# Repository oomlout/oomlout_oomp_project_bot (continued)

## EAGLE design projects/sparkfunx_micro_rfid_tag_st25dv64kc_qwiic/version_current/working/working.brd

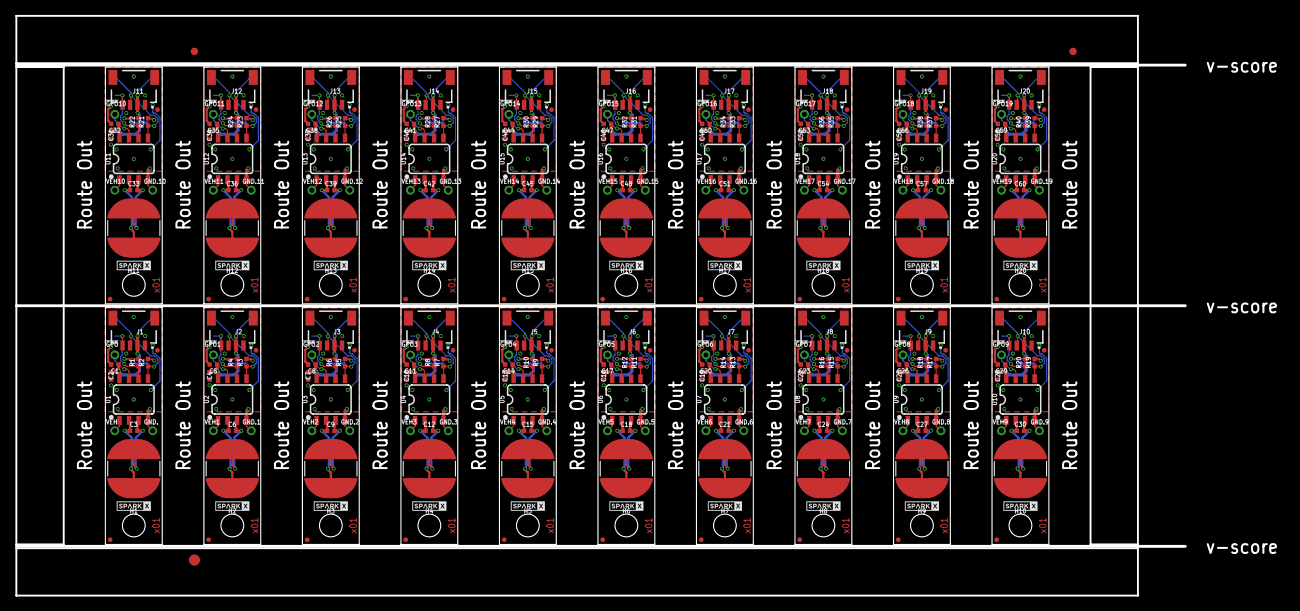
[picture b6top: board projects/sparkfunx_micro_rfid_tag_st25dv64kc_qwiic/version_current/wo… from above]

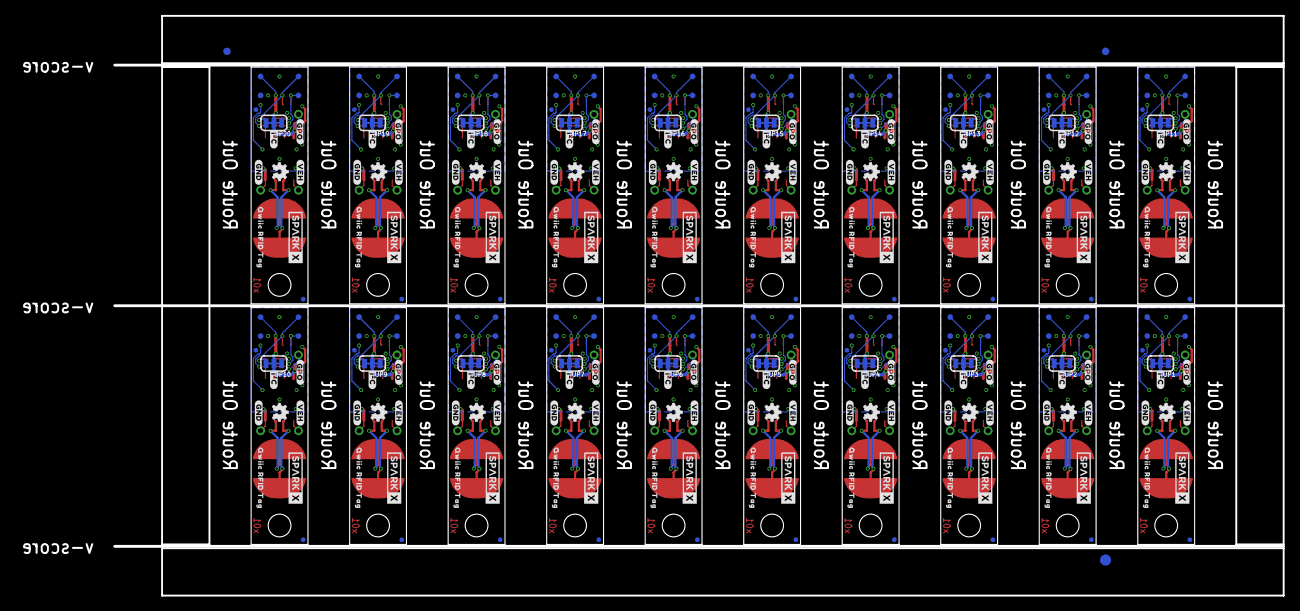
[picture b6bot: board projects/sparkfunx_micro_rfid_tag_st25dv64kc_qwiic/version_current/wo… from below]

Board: 2 copper layers, 156.7 x 77.7 mm, 586 parts (283 on the bottom side), 200 nets.

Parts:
3V1, 3V2, 3V3, 3V4, 3V5, 3V6, 3V7, 3V8, 3V9, 3V10, 3V11, 3V12, 3V13, 3V14, 3V15, 3V16, 3V17, 3V18, 3V19, 3V20: TEST-POINT3; PAD.03X.03
!GPO!, !GPO!1, !GPO!2, !GPO!3, !GPO!4, !GPO!5, !GPO!6, !GPO!7, !GPO!8, !GPO!9, !GPO!10, !GPO!11, !GPO!12, !GPO!13, !GPO!14, !GPO!15, !GPO!16, !GPO!17, !GPO!18, !GPO!19: 1X01_1MM_NO_SILK
ANT, ANT1, ANT2, ANT3, ANT4, ANT5, ANT6, ANT7, ANT8, ANT9, ANT10, ANT11, ANT12, ANT13, ANT14, ANT15, ANT16, ANT17, ANT18, ANT19: 4.7μH; W3102
C1, C5, C8, C11, C14, C17, C20, C23, C26, C29, C32, C35, C38, C41, C44, C47, C50, C53, C56, C59: 0.1uF; 0402-TIGHT
C2, C4, C7, C10, C13, C16, C19, C22, C25, C28, C31, C34, C37, C40, C43, C46, C49, C52, C55, C58: 2.2uF; 0402-TIGHT
C3, C6, C9, C12, C15, C18, C21, C24, C27, C30, C33, C36, C39, C42, C45, C48, C51, C54, C57, C60: 0.5pF; 0402-TIGHT
E$1, E$2, E$3, E$4: FIDUCIAL-1X2
E$5, E$6: FIDUCIAL-1.5X3
FD1, FD2, FD3, FD4, FD5, FD6, FD7, FD8, FD9, FD10, FD11, FD12, FD13, FD14, FD15, FD16, FD17, FD18, FD19, FD20, FD21, FD22, FD23, FD24, FD25, FD26, FD27, FD28, FD29, FD30, FD31, FD32, FD33, FD34, FD35, FD36, FD37, FD38, FD39, FD40, FD41, FD42, FD43, FD44, FD45, FD46, FD47, FD48, FD49, FD50, FD51, FD52, FD53, FD54, FD55, FD56, FD57, FD58, FD59, FD60, FD61, FD62, FD63, FD64, FD65, FD66, FD67, FD68, FD69, FD70, FD71, FD72, FD73, FD74, FD75, FD76, FD77, FD78, FD79, FD80: FIDUCIALUFIDUCIAL; FIDUCIAL-MICRO
GND, GND1, GND2, GND3, GND4, GND5, GND6, GND7, GND8, GND9, GND10, GND11, GND12, GND13, GND14, GND15, GND16, GND17, GND18, GND19: TEST-POINT3; PAD.03X.03
GND., GND.1, GND.2, GND.3, GND.4, GND.5, GND.6, GND.7, GND.8, GND.9, GND.10, GND.11, GND.12, GND.13, GND.14, GND.15, GND.16, GND.17, GND.18, GND.19: 1X01_1MM_NO_SILK
H1, H2, H3, H4, H5, H6, H7, H8, H9, H10, H11, H12, H13, H14, H15, H16, H17, H18, H19, H20: STAND-OFFTIGHT; STAND-OFF-TIGHT
J1, J2, J3, J4, J5, J6, J7, J8, J9, J10, J11, J12, J13, J14, J15, J16, J17, J18, J19, J20: QWIIC_RIGHT_ANGLE; JST04_1MM_RA
JP1, JP2, JP3, JP4, JP5, JP6, JP7, JP8, JP9, JP10, JP11, JP12, JP13, JP14, JP15, JP16, JP17, JP18, JP19, JP20: JUMPER-SMT_3_2-NC_TRACE_SILK; SMT-JUMPER_3_2-NC_TRACE_SILK
LOGO1, LOGO2, LOGO3, LOGO4, LOGO5, LOGO6, LOGO7, LOGO8, LOGO9, LOGO10, LOGO11, LOGO12, LOGO13, LOGO14, LOGO15, LOGO16, LOGO17, LOGO18, LOGO19, LOGO20: OSHW-LOGOMINI; OSHW-LOGO-MINI
R1, R2, R3, R4, R5, R6, R7, R8, R9, R10, R11, R12, R13, R14, R15, R16, R17, R18, R19, R20, R21, R22, R23, R24, R25, R26, R27, R28, R29, R30, R31, R32, R33, R34, R35, R36, R37, R38, R39, R40: 2.2k; 0402-TIGHT
SCL, SCL1, SCL2, SCL3, SCL4, SCL5, SCL6, SCL7, SCL8, SCL9, SCL10, SCL11, SCL12, SCL13, SCL14, SCL15, SCL16, SCL17, SCL18, SCL19: TEST-POINT3; PAD.03X.03
SDA, SDA1, SDA2, SDA3, SDA4, SDA5, SDA6, SDA7, SDA8, SDA9, SDA10, SDA11, SDA12, SDA13, SDA14, SDA15, SDA16, SDA17, SDA18, SDA19: TEST-POINT3; PAD.03X.03
U1, U2, U3, U4, U5, U6, U7, U8, U9, U10, U11, U12, U13, U14, U15, U16, U17, U18, U19, U20: ST25DV64KC; SO08
U$1, U$7, U$14, U$22, U$29, U$36, U$43, U$50, U$57, U$64, U$71, U$78, U$85, U$92, U$99, U$106, U$113, U$120, U$127, U$134: SPARKX-LOGO2; SPARKX-TINY
U$2, U$10, U$17, U$25, U$32, U$39, U$46, U$53, U$60, U$67, U$74, U$81, U$88, U$95, U$102, U$109, U$116, U$123, U$130, U$137: ##GPO##0
U$3, U$13, U$21, U$28, U$35, U$42, U$49, U$56, U$63, U$70, U$77, U$84, U$91, U$98, U$105, U$112, U$119, U$126, U$133, U$140: QWIIC_RFID_TAG0
U$4, U$11, U$18, U$26, U$33, U$40, U$47, U$54, U$61, U$68, U$75, U$82, U$89, U$96, U$103, U$110, U$117, U$124, U$131, U$138: #VEH#0
U$5, U$9, U$16, U$24, U$31, U$38, U$45, U$52, U$59, U$66, U$73, U$80, U$87, U$94, U$101, U$108, U$115, U$122, U$129, U$136: #I�C#0
U$6, U$12, U$19, U$27, U$34, U$41, U$48, U$55, U$62, U$69, U$76, U$83, U$90, U$97, U$104, U$111, U$118, U$125, U$132, U$139: #GND#0
U$8, U$15, U$20, U$23, U$30, U$37, U$44, U$51, U$58, U$65, U$72, U$79, U$86, U$93, U$100, U$107, U$114, U$121, U$128, U$135: SPARKX-LOGO3; SPARKX-SMALL
VEH, VEH1, VEH2, VEH3, VEH4, VEH5, VEH6, VEH7, VEH8, VEH9, VEH10, VEH11, VEH12, VEH13, VEH14, VEH15, VEH16, VEH17, VEH18, VEH19: 1X01_1MM_NO_SILK

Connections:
3.3V: 3V3.1, C1.1, C2.1, J1.2, JP1.2, U1.8
3.3V1: 3V1.1, C4.1, C5.1, J2.2, JP2.2, U2.8
3.3V2: 3V2.1, C7.1, C8.1, J3.2, JP3.2, U3.8
3.3V3: 3V4.1, C10.1, C11.1, J4.2, JP4.2, U4.8
3.3V4: 3V5.1, C13.1, C14.1, J5.2, JP5.2, U5.8
3.3V5: 3V6.1, C16.1, C17.1, J6.2, JP6.2, U6.8
3.3V6: 3V7.1, C19.1, C20.1, J7.2, JP7.2, U7.8
3.3V7: 3V8.1, C22.1, C23.1, J8.2, JP8.2, U8.8
3.3V8: 3V9.1, C25.1, C26.1, J9.2, JP9.2, U9.8
3.3V9: 3V10.1, C28.1, C29.1, J10.2, JP10.2, U10.8
3.3V10: 3V11.1, C31.1, C32.1, J11.2, JP11.2, U11.8
3.3V11: 3V12.1, C34.1, C35.1, J12.2, JP12.2, U12.8
3.3V12: 3V13.1, C37.1, C38.1, J13.2, JP13.2, U13.8
3.3V13: 3V14.1, C40.1, C41.1, J14.2, JP14.2, U14.8
3.3V14: 3V15.1, C43.1, C44.1, J15.2, JP15.2, U15.8
3.3V15: 3V16.1, C46.1, C47.1, J16.2, JP16.2, U16.8
3.3V16: 3V17.1, C49.1, C50.1, J17.2, JP17.2, U17.8
3.3V17: 3V18.1, C52.1, C53.1, J18.2, JP18.2, U18.8
3.3V18: 3V19.1, C55.1, C56.1, J19.2, JP19.2, U19.8
3.3V19: 3V20.1, C58.1, C59.1, J20.2, JP20.2, U20.8
!GPO!: !GPO!.1, U1.7
!GPO!1: !GPO!1.1, U2.7
!GPO!2: !GPO!2.1, U3.7
!GPO!3: !GPO!3.1, U4.7
!GPO!4: !GPO!4.1, U5.7
!GPO!5: !GPO!5.1, U6.7
!GPO!6: !GPO!6.1, U7.7
!GPO!7: !GPO!7.1, U8.7
!GPO!8: !GPO!8.1, U9.7
!GPO!9: !GPO!9.1, U10.7
!GPO!10: !GPO!10.1, U11.7
!GPO!11: !GPO!11.1, U12.7
!GPO!12: !GPO!12.1, U13.7
!GPO!13: !GPO!13.1, U14.7
!GPO!14: !GPO!14.1, U15.7
!GPO!15: !GPO!15.1, U16.7
!GPO!16: !GPO!16.1, U17.7
!GPO!17: !GPO!17.1, U18.7
!GPO!18: !GPO!18.1, U19.7
!GPO!19: !GPO!19.1, U20.7
GND: C1.2, C2.2, GND.1, GND..1, J1.1, U1.4
GND1: C4.2, C5.2, GND1.1, GND.1.1, J2.1, U2.4
GND2: C7.2, C8.2, GND2.1, GND.2.1, J3.1, U3.4
GND3: C10.2, C11.2, GND3.1, GND.3.1, J4.1, U4.4
GND4: C13.2, C14.2, GND4.1, GND.4.1, J5.1, U5.4
GND5: C16.2, C17.2, GND5.1, GND.5.1, J6.1, U6.4
GND6: C19.2, C20.2, GND6.1, GND.6.1, J7.1, U7.4
GND7: C22.2, C23.2, GND7.1, GND.7.1, J8.1, U8.4
GND8: C25.2, C26.2, GND8.1, GND.8.1, J9.1, U9.4
GND9: C28.2, C29.2, GND9.1, GND.9.1, J10.1, U10.4
GND10: C31.2, C32.2, GND10.1, GND.10.1, J11.1, U11.4
GND11: C34.2, C35.2, GND11.1, GND.11.1, J12.1, U12.4
GND12: C37.2, C38.2, GND12.1, GND.12.1, J13.1, U13.4
GND13: C40.2, C41.2, GND13.1, GND.13.1, J14.1, U14.4
GND14: C43.2, C44.2, GND14.1, GND.14.1, J15.1, U15.4
GND15: C46.2, C47.2, GND15.1, GND.15.1, J16.1, U16.4
GND16: C49.2, C50.2, GND16.1, GND.16.1, J17.1, U17.4
GND17: C52.2, C53.2, GND17.1, GND.17.1, J18.1, U18.4
GND18: C55.2, C56.2, GND18.1, GND.18.1, J19.1, U19.4
GND19: C58.2, C59.2, GND19.1, GND.19.1, J20.1, U20.4
unnamed: ANT.2, C3.2, U1.3
unnamed: ANT.1, C3.1, U1.2
unnamed: JP1.3, R2.2
unnamed: JP1.1, R1.2
unnamed: ANT1.2, C6.2, U2.3
unnamed: ANT1.1, C6.1, U2.2
unnamed: JP2.3, R3.2
unnamed: JP2.1, R4.2
unnamed: ANT2.2, C9.2, U3.3
unnamed: ANT2.1, C9.1, U3.2
unnamed: JP3.3, R5.2
unnamed: JP3.1, R6.2
unnamed: ANT3.2, C12.2, U4.3
unnamed: ANT3.1, C12.1, U4.2
unnamed: JP4.3, R7.2
unnamed: JP4.1, R8.2
unnamed: ANT4.2, C15.2, U5.3
unnamed: ANT4.1, C15.1, U5.2
unnamed: JP5.3, R9.2
unnamed: JP5.1, R10.2
unnamed: ANT5.2, C18.2, U6.3
unnamed: ANT5.1, C18.1, U6.2
unnamed: JP6.3, R11.2
unnamed: JP6.1, R12.2
unnamed: ANT6.2, C21.2, U7.3
unnamed: ANT6.1, C21.1, U7.2
unnamed: JP7.3, R13.2
unnamed: JP7.1, R14.2
unnamed: ANT7.2, C24.2, U8.3
unnamed: ANT7.1, C24.1, U8.2
unnamed: JP8.3, R15.2
unnamed: JP8.1, R16.2
unnamed: ANT8.2, C27.2, U9.3
unnamed: ANT8.1, C27.1, U9.2
unnamed: JP9.3, R17.2
unnamed: JP9.1, R18.2
unnamed: ANT9.2, C30.2, U10.3
unnamed: ANT9.1, C30.1, U10.2
unnamed: JP10.3, R19.2
unnamed: JP10.1, R20.2
unnamed: ANT10.2, C33.2, U11.3
unnamed: ANT10.1, C33.1, U11.2
unnamed: JP11.3, R21.2
unnamed: JP11.1, R22.2
unnamed: ANT11.2, C36.2, U12.3
unnamed: ANT11.1, C36.1, U12.2
unnamed: JP12.3, R23.2
unnamed: JP12.1, R24.2
unnamed: ANT12.2, C39.2, U13.3
unnamed: ANT12.1, C39.1, U13.2
unnamed: JP13.3, R25.2
unnamed: JP13.1, R26.2
unnamed: ANT13.2, C42.2, U14.3
unnamed: ANT13.1, C42.1, U14.2
unnamed: JP14.3, R27.2
unnamed: JP14.1, R28.2
unnamed: ANT14.2, C45.2, U15.3
unnamed: ANT14.1, C45.1, U15.2
unnamed: JP15.3, R29.2
unnamed: JP15.1, R30.2
unnamed: ANT15.2, C48.2, U16.3
unnamed: ANT15.1, C48.1, U16.2
unnamed: JP16.3, R31.2
unnamed: JP16.1, R32.2
unnamed: ANT16.2, C51.2, U17.3
unnamed: ANT16.1, C51.1, U17.2
unnamed: JP17.3, R33.2
unnamed: JP17.1, R34.2
unnamed: ANT17.2, C54.2, U18.3
unnamed: ANT17.1, C54.1, U18.2
unnamed: JP18.3, R35.2
unnamed: JP18.1, R36.2
unnamed: ANT18.2, C57.2, U19.3
unnamed: ANT18.1, C57.1, U19.2
unnamed: JP19.3, R37.2
unnamed: JP19.1, R38.2
unnamed: ANT19.2, C60.2, U20.3
unnamed: ANT19.1, C60.1, U20.2
unnamed: JP20.3, R39.2
unnamed: JP20.1, R40.2
SCL: J1.4, R1.1, SCL.1, U1.6
SCL1: J2.4, R4.1, SCL1.1, U2.6
SCL2: J3.4, R6.1, SCL2.1, U3.6
SCL3: J4.4, R8.1, SCL3.1, U4.6
SCL4: J5.4, R10.1, SCL4.1, U5.6
SCL5: J6.4, R12.1, SCL5.1, U6.6
SCL6: J7.4, R14.1, SCL6.1, U7.6
SCL7: J8.4, R16.1, SCL7.1, U8.6
SCL8: J9.4, R18.1, SCL8.1, U9.6
SCL9: J10.4, R20.1, SCL9.1, U10.6
SCL10: J11.4, R22.1, SCL10.1, U11.6
SCL11: J12.4, R24.1, SCL11.1, U12.6
SCL12: J13.4, R26.1, SCL12.1, U13.6
SCL13: J14.4, R28.1, SCL13.1, U14.6
SCL14: J15.4, R30.1, SCL14.1, U15.6
SCL15: J16.4, R32.1, SCL15.1, U16.6
SCL16: J17.4, R34.1, SCL16.1, U17.6
SCL17: J18.4, R36.1, SCL17.1, U18.6
SCL18: J19.4, R38.1, SCL18.1, U19.6
SCL19: J20.4, R40.1, SCL19.1, U20.6
SDA: J1.3, R2.1, SDA.1, U1.5
SDA1: J2.3, R3.1, SDA1.1, U2.5
SDA2: J3.3, R5.1, SDA2.1, U3.5
SDA3: J4.3, R7.1, SDA3.1, U4.5
SDA4: J5.3, R9.1, SDA4.1, U5.5
SDA5: J6.3, R11.1, SDA5.1, U6.5
SDA6: J7.3, R13.1, SDA6.1, U7.5
SDA7: J8.3, R15.1, SDA7.1, U8.5
SDA8: J9.3, R17.1, SDA8.1, U9.5
SDA9: J10.3, R19.1, SDA9.1, U10.5
SDA10: J11.3, R21.1, SDA10.1, U11.5
SDA11: J12.3, R23.1, SDA11.1, U12.5
SDA12: J13.3, R25.1, SDA12.1, U13.5
SDA13: J14.3, R27.1, SDA13.1, U14.5
SDA14: J15.3, R29.1, SDA14.1, U15.5
SDA15: J16.3, R31.1, SDA15.1, U16.5
SDA16: J17.3, R33.1, SDA16.1, U17.5
SDA17: J18.3, R35.1, SDA17.1, U18.5
SDA18: J19.3, R37.1, SDA18.1, U19.5
SDA19: J20.3, R39.1, SDA19.1, U20.5
VEH: U1.1, VEH.1
VEH1: U2.1, VEH1.1
VEH2: U3.1, VEH2.1
VEH3: U4.1, VEH3.1
VEH4: U5.1, VEH4.1
VEH5: U6.1, VEH5.1
VEH6: U7.1, VEH6.1
VEH7: U8.1, VEH7.1
VEH8: U9.1, VEH8.1
VEH9: U10.1, VEH9.1
VEH10: U11.1, VEH10.1
VEH11: U12.1, VEH11.1
VEH12: U13.1, VEH12.1
VEH13: U14.1, VEH13.1
VEH14: U15.1, VEH14.1
VEH15: U16.1, VEH15.1
VEH16: U17.1, VEH16.1
VEH17: U18.1, VEH17.1
VEH18: U19.1, VEH18.1
VEH19: U20.1, VEH19.1

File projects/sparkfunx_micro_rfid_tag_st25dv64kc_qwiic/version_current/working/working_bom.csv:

"Id";"Designator";"Footprint";"Quantity";"Designation";"Supplier and ref";
1;"R16,R22,R8,R3,R33,R5,R14,R18,R4,R21,R23,R31,R40,R37,R7,R38,R2,R13,R17,R9,R32,R6,R15,R11,R28,R19,R36,R29,R12,R20,R1,R30,R25,R26,R39,R10,R24,R27,R34,R35";"0402-TIGHT";40;"2.2k";;;
2;"FD53,FD51,FD25,FD13,FD9,FD47,FD31,FD37,FD15,FD3,FD67,FD55,FD71,FD29,FD75,FD19,FD33,FD41,FD11,FD7,FD59,FD5,FD69,FD63,FD17,FD43,FD49,FD57,FD27,FD45,FD65,FD23,FD61,FD39,FD73,FD1,FD77,FD21,FD79,FD35,FD20,FD58,FD26,FD18,FD66,FD52,FD40,FD38,FD12,FD72,FD36,FD16,FD28,FD10,FD32,FD48,FD42,FD30,FD68,FD64,FD76,FD80,FD74,FD56,FD24,FD46,FD34,FD8,FD22,FD54,FD70,FD60,FD14,FD6,FD2,FD78,FD44,FD62,FD4,FD50";"FIDUCIAL-MICRO";80;"FIDUCIALUFIDUCIAL";;;
3;"H1,H14,H20,H8,H3,H9,H18,H17,H4,H12,H13,H11,H2,H19,H15,H6,H10,H7,H5,H16";"STAND-OFF-TIGHT";20;"STAND-OFFTIGHT";;;
4;"GND.18,VEH10,GND.13,VEH12,GND.4,GND.7,GND.10,!GPO!3,!GPO!18,!GPO!7,VEH16,VEH4,GND.12,GND.14,VEH3,VEH6,!GPO!13,!GPO!2,!GPO!0,VEH8,!GPO!15,GND.0,!GPO!19,VEH13,GND.1,VEH1,VEH7,!GPO!8,VEH2,GND.11,!GPO!5,GND.16,GND.8,VEH11,!GPO!12,VEH9,VEH17,!GPO!6,!GPO!11,VEH14,!GPO!1,VEH18,GND.6,GND.5,!GPO!9,GND.15,VEH15,GND.17,!GPO!16,VEH0,!GPO!14,!GPO!17,GND.2,GND.9,!GPO!4,GND.19,GND.3,!GPO!10,VEH19,VEH5";"1X01_1MM_NO_SILK";60;"";;;
5;"U$120,U$99,U$43,U$113,U$127,U$14,U$71,U$7,U$57,U$50,U$22,U$78,U$92,U$64,U$85,U$29,U$106,U$134,U$36,U$1";"SPARKX-TINY";20;"SPARKX-LOGO2";;;
6;"C39,C60,C42,C30,C45,C51,C3,C21,C12,C48,C9,C33,C57,C18,C36,C27,C24,C54,C15,C6";"0402-TIGHT";20;"0.5pF";;;
7;"U1,U20,U2,U12,U8,U6,U10,U17,U4,U11,U13,U16,U18,U9,U15,U3,U14,U19,U7,U5";"SO08";20;"ST25DV64KC";;;
8;"C11,C41,C29,C8,C17,C44,C53,C50,C59,C20,C38,C26,C47,C5,C32,C56,C23,C14,C35,C1";"0402-TIGHT";20;"0.1uF";;;
9;"J9,J2,J17,J6,J10,J20,J13,J8,J15,J14,J11,J18,J3,J4,J19,J1,J16,J5,J12,J7";"JST04_1MM_RA";20;"QWIIC_RIGHT_ANGLE";;;
10;"ANT19,ANT18,ANT16,ANT12,ANT9,ANT0,ANT3,ANT17,ANT11,ANT15,ANT8,ANT5,ANT10,ANT14,ANT7,ANT13,ANT6,ANT4,ANT1,ANT2";"W3102";20;"4.7μH";;;
11;"C58,C7,C2,C37,C19,C46,C25,C22,C4,C31,C28,C52,C40,C49,C43,C13,C34,C16,C10,C55";"0402-TIGHT";20;"2.2uF";;;
12;"E$3,E$1,E$4,E$2";"FIDUCIAL-1X2";4;"";;;
13;"E$5,E$6";"FIDUCIAL-1.5X3";2;"";;;
14;"SDA19,UNK3V14,UNK3V12,UNK3V20,UNK3V5,UNK3V3,SDA6,UNK3V13,GND15,SCL2,SCL15,UNK3V18,GND3,GND0,GND2,SCL12,GND14,SDA12,SDA1,GND10,SCL7,GND5,GND6,SDA2,SCL0,SCL5,SCL11,SDA18,UNK3V11,SCL4,SDA14,GND4,GND17,GND19,SCL13,UNK3V10,GND16,SDA3,SCL6,SCL10,UNK3V8,UNK3V17,SDA8,SDA13,SCL8,SDA11,SCL1,SCL9,GND7,SCL19,SDA9,SDA5,SDA15,SDA4,UNK3V4,GND9,SDA17,UNK3V7,SCL16,UNK3V9,UNK3V16,SDA7,SDA16,UNK3V2,SCL3,GND13,SCL14,GND11,SDA10,SDA0,GND1,UNK3V19,SCL17,GND18,UNK3V6,UNK3V1,SCL18,GND12,GND8,UNK3V15";"PAD.03X.03";80;"TEST-POINT3";;;
15;"U$105,U$3,U$13,U$21,U$126,U$70,U$28,U$98,U$77,U$63,U$91,U$112,U$119,U$133,U$35,U$84,U$42,U$140,U$49,U$56";"QWIIC_RFID_TAG0";20;"";;;
16;"U$41,U$69,U$139,U$90,U$76,U$34,U$125,U$104,U$132,U$12,U$55,U$62,U$83,U$118,U$19,U$97,U$48,U$111,U$27,U$6";"#GND#0";20;"";;;
17;"LOGO12,LOGO16,LOGO1,LOGO17,LOGO11,LOGO9,LOGO14,LOGO7,LOGO2,LOGO19,LOGO3,LOGO18,LOGO6,LOGO13,LOGO4,LOGO15,LOGO10,LOGO20,LOGO5,LOGO8";"OSHW-LOGO-MINI";20;"OSHW-LOGOMINI";;;
18;"U$38,U$5,U$66,U$101,U$59,U$94,U$122,U$108,U$136,U$115,U$129,U$16,U$52,U$31,U$80,U$87,U$73,U$24,U$9,U$45";"#I�C#0";20;"";;;
19;"U$30,U$20,U$121,U$65,U$114,U$23,U$51,U$128,U$86,U$93,U$107,U$8,U$100,U$15,U$58,U$135,U$72,U$44,U$79,U$37";"SPARKX-SMALL";20;"SPARKX-LOGO3";;;
20;"U$53,U$137,U$17,U$32,U$39,U$67,U$60,U$81,U$109,U$95,U$25,U$74,U$130,U$10,U$123,U$102,U$116,U$2,U$88,U$46";"##GPO##0";20;"";;;
21;"JP6,JP9,JP7,JP14,JP8,JP3,JP1,JP11,JP20,JP2,JP4,JP13,JP17,JP16,JP19,JP5,JP12,JP15,JP18,JP10";"SMT-JUMPER_3_2-NC_TRACE_SILK";20;"JUMPER-SMT_3_2-NC_TRACE_SILK";;;
22;"U$18,U$11,U$4,U$89,U$61,U$124,U$110,U$33,U$26,U$138,U$75,U$68,U$131,U$54,U$47,U$82,U$96,U$117,U$40,U$103";"#VEH#0";20;"";;;

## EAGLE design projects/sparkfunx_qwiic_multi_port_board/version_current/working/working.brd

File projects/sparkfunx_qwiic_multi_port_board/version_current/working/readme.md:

# Qwiic_Multi_Port_Board by sparkfunX  
This is a harvested standardized copy of a project from github.  
The original project can be found at:  
https://github.com/sparkfunX/Qwiic_Multi_Port_Board  
Please consult that link for additional, details, files, and license information.  
Note: It was auto harvested and if the original repo had more than one board file or anything out of the ordinary the files here are likely not representative.

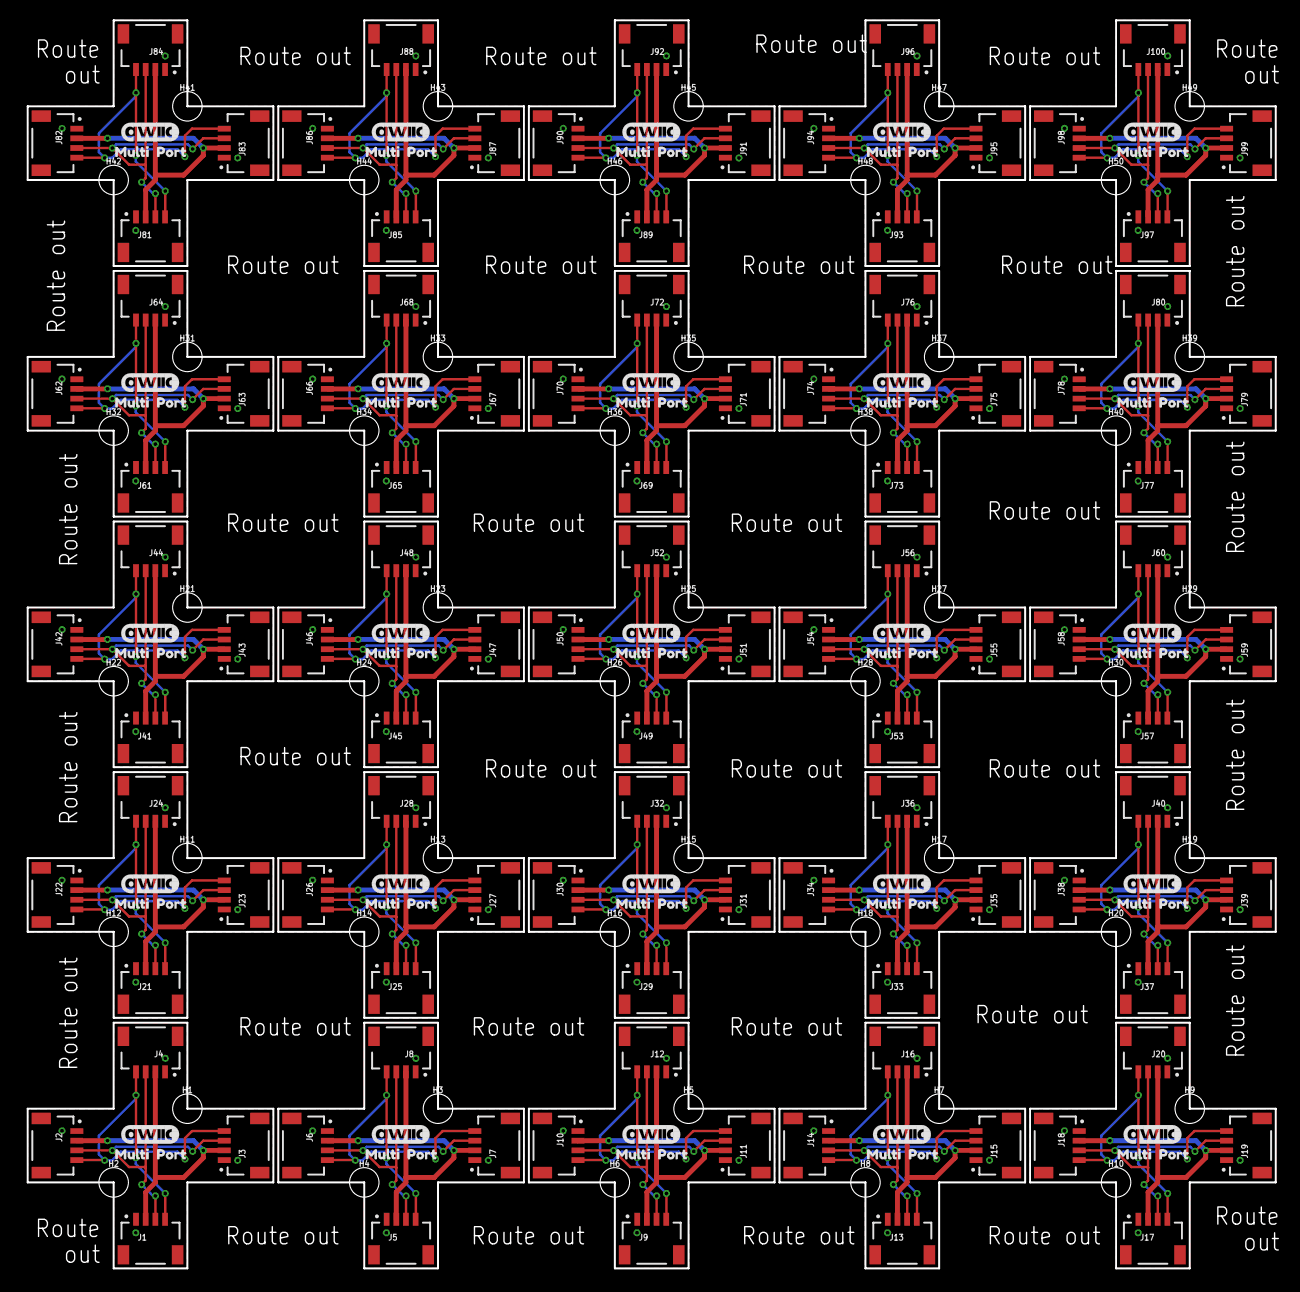
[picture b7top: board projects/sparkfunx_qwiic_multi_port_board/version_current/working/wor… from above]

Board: 2 copper layers, 129.0 x 129.0 mm, 325 parts (100 on the bottom side), 100 nets.

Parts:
H1, H2, H3, H4, H5, H6, H7, H8, H9, H10, H11, H12, H13, H14, H15, H16, H17, H18, H19, H20, H21, H22, H23, H24, H25, H26, H27, H28, H29, H30, H31, H32, H33, H34, H35, H36, H37, H38, H39, H40, H41, H42, H43, H44, H45, H46, H47, H48, H49, H50: STAND-OFFTIGHT; STAND-OFF-TIGHT
J1, J2, J3, J4, J5, J6, J7, J8, J9, J10, J11, J12, J13, J14, J15, J16, J17, J18, J19, J20, J21, J22, J23, J24, J25, J26, J27, J28, J29, J30, J31, J32, J33, J34, J35, J36, J37, J38, J39, J40, J41, J42, J43, J44, J45, J46, J47, J48, J49, J50, J51, J52, J53, J54, J55, J56, J57, J58, J59, J60, J61, J62, J63, J64, J65, J66, J67, J68, J69, J70, J71, J72, J73, J74, J75, J76, J77, J78, J79, J80, J81, J82, J83, J84, J85, J86, J87, J88, J89, J90, J91, J92, J93, J94, J95, J96, J97, J98, J99, J100: QWIIC_RIGHT_ANGLE; JST04_1MM_RA
U$1, U$3, U$11, U$12, U$18, U$19, U$25, U$26, U$32, U$33, U$39, U$40, U$46, U$47, U$53, U$54, U$60, U$61, U$67, U$68, U$74, U$75, U$81, U$82, U$88, U$89, U$95, U$96, U$102, U$103, U$109, U$110, U$116, U$117, U$123, U$124, U$130, U$131, U$137, U$138, U$144, U$145, U$151, U$152, U$158, U$159, U$165, U$166, U$172, U$173: QWIIC_6MM
U$2, U$6, U$15, U$22, U$29, U$36, U$43, U$50, U$57, U$64, U$71, U$78, U$85, U$92, U$99, U$106, U$113, U$120, U$127, U$134, U$141, U$148, U$155, U$162, U$169: SPARKX-SMALL
U$4, U$7, U$9, U$13, U$16, U$20, U$23, U$27, U$30, U$34, U$37, U$41, U$44, U$48, U$51, U$55, U$58, U$62, U$65, U$69, U$72, U$76, U$79, U$83, U$86, U$90, U$93, U$97, U$100, U$104, U$107, U$111, U$114, U$118, U$121, U$125, U$128, U$132, U$135, U$139, U$142, U$146, U$149, U$153, U$156, U$160, U$163, U$167, U$170, U$174: MULTI1
U$5, U$8, U$10, U$14, U$17, U$21, U$24, U$28, U$31, U$35, U$38, U$42, U$45, U$49, U$52, U$56, U$59, U$63, U$66, U$70, U$73, U$77, U$80, U$84, U$87, U$91, U$94, U$98, U$101, U$105, U$108, U$112, U$115, U$119, U$122, U$126, U$129, U$133, U$136, U$140, U$143, U$147, U$150, U$154, U$157, U$161, U$164, U$168, U$171, U$175: PORT2

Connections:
3.3V: J1.2, J2.2, J3.2, J4.2
3.3V1: J5.2, J6.2, J7.2, J8.2
3.3V2: J9.2, J10.2, J11.2, J12.2
3.3V3: J13.2, J14.2, J15.2, J16.2
3.3V4: J17.2, J18.2, J19.2, J20.2
3.3V5: J21.2, J22.2, J23.2, J24.2
3.3V6: J25.2, J26.2, J27.2, J28.2
3.3V7: J29.2, J30.2, J31.2, J32.2
3.3V8: J33.2, J34.2, J35.2, J36.2
3.3V9: J37.2, J38.2, J39.2, J40.2
3.3V10: J41.2, J42.2, J43.2, J44.2
3.3V11: J45.2, J46.2, J47.2, J48.2
3.3V12: J49.2, J50.2, J51.2, J52.2
3.3V13: J53.2, J54.2, J55.2, J56.2
3.3V14: J57.2, J58.2, J59.2, J60.2
3.3V15: J61.2, J62.2, J63.2, J64.2
3.3V16: J65.2, J66.2, J67.2, J68.2
3.3V17: J69.2, J70.2, J71.2, J72.2
3.3V18: J73.2, J74.2, J75.2, J76.2
3.3V19: J77.2, J78.2, J79.2, J80.2
3.3V20: J81.2, J82.2, J83.2, J84.2
3.3V21: J85.2, J86.2, J87.2, J88.2
3.3V22: J89.2, J90.2, J91.2, J92.2
3.3V23: J93.2, J94.2, J95.2, J96.2
3.3V24: J97.2, J98.2, J99.2, J100.2
GND: J1.1, J2.1, J3.1, J4.1
GND1: J5.1, J6.1, J7.1, J8.1
GND2: J9.1, J10.1, J11.1, J12.1
GND3: J13.1, J14.1, J15.1, J16.1
GND4: J17.1, J18.1, J19.1, J20.1
GND5: J21.1, J22.1, J23.1, J24.1
GND6: J25.1, J26.1, J27.1, J28.1
GND7: J29.1, J30.1, J31.1, J32.1
GND8: J33.1, J34.1, J35.1, J36.1
GND9: J37.1, J38.1, J39.1, J40.1
GND10: J41.1, J42.1, J43.1, J44.1
GND11: J45.1, J46.1, J47.1, J48.1
GND12: J49.1, J50.1, J51.1, J52.1
GND13: J53.1, J54.1, J55.1, J56.1
GND14: J57.1, J58.1, J59.1, J60.1
GND15: J61.1, J62.1, J63.1, J64.1
GND16: J65.1, J66.1, J67.1, J68.1
GND17: J69.1, J70.1, J71.1, J72.1
GND18: J73.1, J74.1, J75.1, J76.1
GND19: J77.1, J78.1, J79.1, J80.1
GND20: J81.1, J82.1, J83.1, J84.1
GND21: J85.1, J86.1, J87.1, J88.1
GND22: J89.1, J90.1, J91.1, J92.1
GND23: J93.1, J94.1, J95.1, J96.1
GND24: J97.1, J98.1, J99.1, J100.1
SCL: J1.4, J2.4, J3.4, J4.4
SCL1: J5.4, J6.4, J7.4, J8.4
SCL2: J9.4, J10.4, J11.4, J12.4
SCL3: J13.4, J14.4, J15.4, J16.4
SCL4: J17.4, J18.4, J19.4, J20.4
SCL5: J21.4, J22.4, J23.4, J24.4
SCL6: J25.4, J26.4, J27.4, J28.4
SCL7: J29.4, J30.4, J31.4, J32.4
SCL8: J33.4, J34.4, J35.4, J36.4
SCL9: J37.4, J38.4, J39.4, J40.4
SCL10: J41.4, J42.4, J43.4, J44.4
SCL11: J45.4, J46.4, J47.4, J48.4
SCL12: J49.4, J50.4, J51.4, J52.4
SCL13: J53.4, J54.4, J55.4, J56.4
SCL14: J57.4, J58.4, J59.4, J60.4
SCL15: J61.4, J62.4, J63.4, J64.4
SCL16: J65.4, J66.4, J67.4, J68.4
SCL17: J69.4, J70.4, J71.4, J72.4
SCL18: J73.4, J74.4, J75.4, J76.4
SCL19: J77.4, J78.4, J79.4, J80.4
SCL20: J81.4, J82.4, J83.4, J84.4
SCL21: J85.4, J86.4, J87.4, J88.4
SCL22: J89.4, J90.4, J91.4, J92.4
SCL23: J93.4, J94.4, J95.4, J96.4
SCL24: J97.4, J98.4, J99.4, J100.4
SDA: J1.3, J2.3, J3.3, J4.3
SDA1: J5.3, J6.3, J7.3, J8.3
SDA2: J9.3, J10.3, J11.3, J12.3
SDA3: J13.3, J14.3, J15.3, J16.3
SDA4: J17.3, J18.3, J19.3, J20.3
SDA5: J21.3, J22.3, J23.3, J24.3
SDA6: J25.3, J26.3, J27.3, J28.3
SDA7: J29.3, J30.3, J31.3, J32.3
SDA8: J33.3, J34.3, J35.3, J36.3
SDA9: J37.3, J38.3, J39.3, J40.3
SDA10: J41.3, J42.3, J43.3, J44.3
SDA11: J45.3, J46.3, J47.3, J48.3
SDA12: J49.3, J50.3, J51.3, J52.3
SDA13: J53.3, J54.3, J55.3, J56.3
SDA14: J57.3, J58.3, J59.3, J60.3
SDA15: J61.3, J62.3, J63.3, J64.3
SDA16: J65.3, J66.3, J67.3, J68.3
SDA17: J69.3, J70.3, J71.3, J72.3
SDA18: J73.3, J74.3, J75.3, J76.3
SDA19: J77.3, J78.3, J79.3, J80.3
SDA20: J81.3, J82.3, J83.3, J84.3
SDA21: J85.3, J86.3, J87.3, J88.3
SDA22: J89.3, J90.3, J91.3, J92.3
SDA23: J93.3, J94.3, J95.3, J96.3
SDA24: J97.3, J98.3, J99.3, J100.3

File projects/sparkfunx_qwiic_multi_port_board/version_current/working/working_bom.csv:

"Id";"Designator";"Footprint";"Quantity";"Designation";"Supplier and ref";
1;"J68,J1,J99,J35,J72,J90,J18,J33,J74,J79,J29,J13,J8,J93,J54,J52,J11,J20,J92,J32,J100,J21,J73,J2,J24,J63,J15,J98,J84,J96,J47,J39,J37,J70,J44,J69,J43,J5,J22,J51,J41,J86,J83,J17,J75,J16,J25,J82,J67,J80,J48,J46,J97,J36,J95,J78,J65,J66,J4,J40,J34,J58,J71,J28,J50,J62,J59,J12,J26,J30,J27,J85,J23,J7,J19,J94,J49,J3,J87,J31,J81,J38,J55,J45,J56,J53,J42,J60,J14,J10,J6,J77,J61,J76,J89,J57,J88,J64,J91,J9";"JST04_1MM_RA";100;"QWIIC_RIGHT_ANGLE";;;
2;"U$74,U$46,U$67,U$81,U$109,U$158,U$116,U$88,U$130,U$172,U$32,U$144,U$1,U$165,U$53,U$11,U$151,U$123,U$18,U$60,U$137,U$39,U$95,U$102,U$25,U$110,U$103,U$26,U$12,U$75,U$159,U$131,U$117,U$54,U$89,U$40,U$68,U$61,U$166,U$145,U$47,U$138,U$3,U$19,U$33,U$124,U$173,U$82,U$96,U$152";"QWIIC_6MM";50;"";;;
3;"H22,H13,H39,H32,H12,H4,H17,H20,H15,H1,H3,H23,H43,H35,H27,H29,H6,H14,H36,H7,H48,H5,H18,H46,H44,H8,H9,H49,H10,H26,H19,H21,H33,H38,H28,H34,H40,H37,H41,H30,H42,H47,H24,H45,H31,H50,H2,H16,H11,H25";"STAND-OFF-TIGHT";50;"STAND-OFFTIGHT";;;
4;"U$107,U$149,U$65,U$156,U$4,U$93,U$9,U$142,U$51,U$79,U$16,U$100,U$23,U$44,U$121,U$128,U$30,U$58,U$114,U$170,U$37,U$163,U$72,U$86,U$135,U$76,U$7,U$153,U$167,U$13,U$55,U$111,U$69,U$139,U$83,U$118,U$97,U$146,U$160,U$90,U$125,U$174,U$48,U$132,U$62,U$41,U$104,U$20,U$34,U$27";"MULTI1";50;"";;;
5;"U$5,U$31,U$45,U$24,U$171,U$66,U$150,U$38,U$73,U$10,U$80,U$143,U$122,U$87,U$101,U$136,U$108,U$164,U$52,U$129,U$59,U$17,U$157,U$94,U$115,U$126,U$105,U$70,U$28,U$161,U$98,U$84,U$91,U$147,U$8,U$175,U$112,U$77,U$14,U$119,U$56,U$133,U$63,U$154,U$42,U$140,U$168,U$49,U$35,U$21";"PORT2";50;"";;;
6;"U$92,U$134,U$2,U$155,U$6,U$106,U$85,U$36,U$22,U$99,U$71,U$127,U$64,U$148,U$29,U$120,U$78,U$113,U$50,U$169,U$162,U$57,U$15,U$43,U$141";"SPARKX-SMALL";25;"";;;
